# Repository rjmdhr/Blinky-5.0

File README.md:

# Blinky-5.0
A "hello world" intro to PCB design provided by Contextual Electronics. I thought I should start out small before I get into more advanced projects I have in mind.

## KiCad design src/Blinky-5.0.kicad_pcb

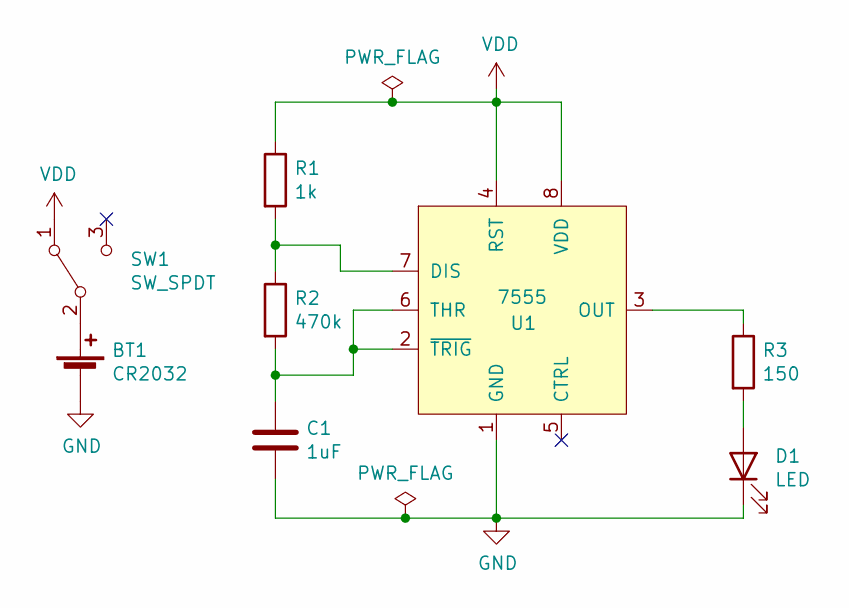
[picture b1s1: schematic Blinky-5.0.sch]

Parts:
BT1: CR2032; 3034
C1: 1uF; C_1206_3216Metric_Pad1.33x1.80mm_HandSolder
D1: LED; LED_1206_3216Metric_Pad1.42x1.75mm_HandSolder
R1: 1k; R_1206_3216Metric_Pad1.30x1.75mm_HandSolder
R2: 470k; R_1206_3216Metric_Pad1.30x1.75mm_HandSolder
R3: 150; R_1206_3216Metric_Pad1.30x1.75mm_HandSolder
SW1: SW_SPDT; JS102011SCQN
U1: 7555; SOIC-8_3.9x4.9mm_P1.27mm

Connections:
GND: BT1.2 (-), C1.2, D1.1 (K), U1.1 (GND)
unnamed: BT1.1 (+), SW1.2 (B)
unnamed: C1.1, R2.2, U1.2 (~TRIG), U1.6 (THR)
unnamed: D1.2 (A), R3.2
unnamed: R1.2, R2.1, U1.7 (DIS)
unnamed: R3.1, U1.3 (OUT)
VDD: R1.1, SW1.1 (A), U1.4 (RST), U1.8 (VDD)

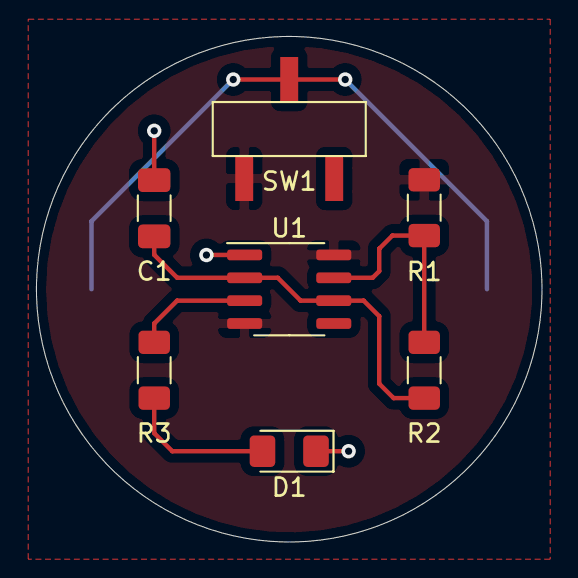
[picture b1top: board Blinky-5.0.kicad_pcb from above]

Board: 2 copper layers, 28.1 x 28.1 mm, 8 parts (1 on the bottom side), 7 nets.

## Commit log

2021-05-03 Add documentation and source folders
2021-05-03 Make schematic
2021-05-05 Add custom library and additions
2021-05-06 Make some custom footprints and define board layout
2021-05-21 Add some changes and finish layout
2021-06-14 Add report
2021-06-14 Fixes
2021-09-05 Update report
